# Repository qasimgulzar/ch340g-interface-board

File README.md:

# CH340G Interface Board

This repository contains the design files and documentation for a CH340G Interface Board, which is used to facilitate
communication between a computer and microcontroller-based projects via USB.

### Screenshots

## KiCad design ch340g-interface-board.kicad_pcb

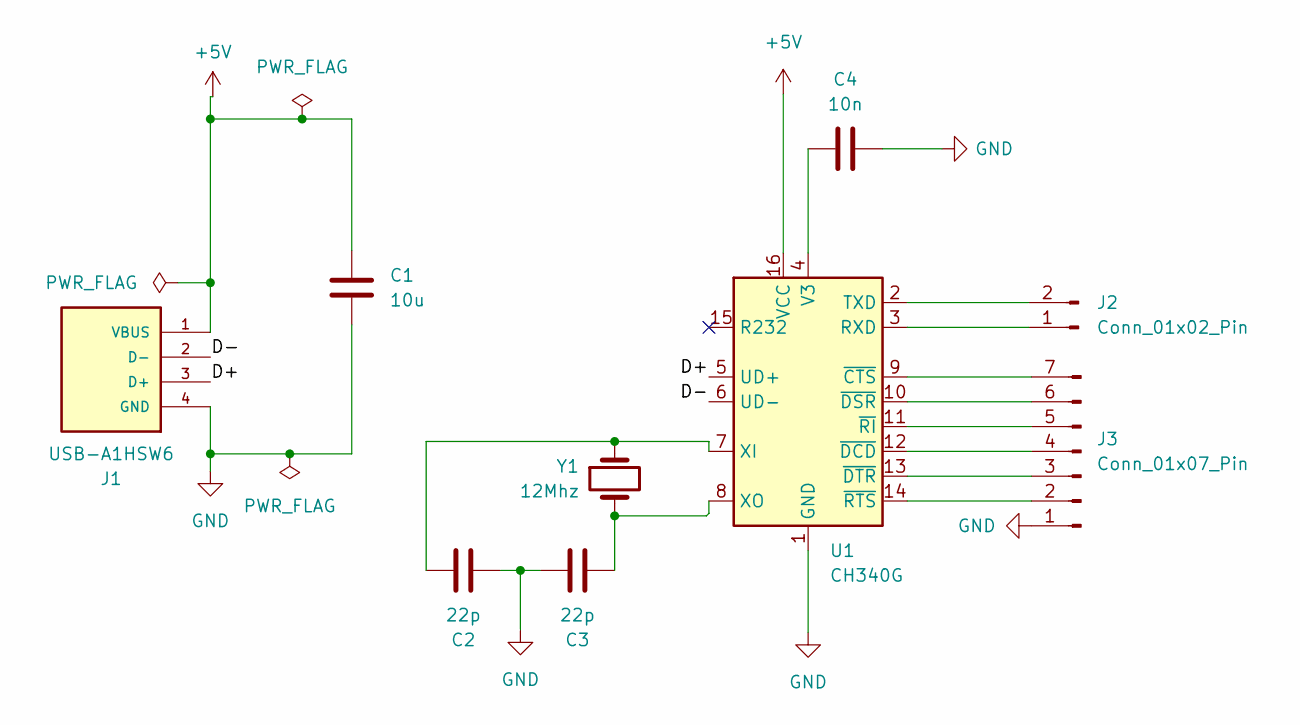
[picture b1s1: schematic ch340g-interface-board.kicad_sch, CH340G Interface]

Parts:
C1: 10u; CP_Radial_D4.0mm_P2.00mm
C2, C3: 22p; C_Disc_D3.0mm_W1.6mm_P2.50mm
C4: 10n; C_Disc_D3.0mm_W1.6mm_P2.50mm
J1: USB-A1HSW6; OST_USB-A1HSW6; PARTREV A
J2: Conn_01x02_Pin; PinHeader_1x02_P1.00mm_Vertical
J3: Conn_01x07_Pin; PinHeader_1x07_P1.00mm_Vertical
U1: CH340G; SOIC-16_3.9x9.9mm_P1.27mm
Y1: 12Mhz; Crystal_HC18-U_Vertical

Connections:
+5V: C1.1, J1.1 (VBUS), U1.16 (VCC)
/D+: J1.3 (D+), U1.5 (UD+)
/D-: J1.2 (D-), U1.6 (UD-)
GND: C1.2, C2.2, C3.1, C4.2, J1.4 (GND), J3.1, U1.1 (GND)
unnamed: J2.1, U1.3 (RXD)
unnamed: J2.2, U1.2 (TXD)
unnamed: J3.2, U1.14 (~RTS)
unnamed: J3.3, U1.13 (~DTR)
unnamed: J3.4, U1.12 (~DCD)
unnamed: J3.5, U1.11 (~RI)
unnamed: J3.6, U1.10 (~DSR)
unnamed: J3.7, U1.9 (~CTS)
unnamed: C4.1, U1.4 (V3)
unnamed: C2.1, U1.7 (XI), Y1.1
unnamed: C3.2, U1.8 (XO), Y1.2

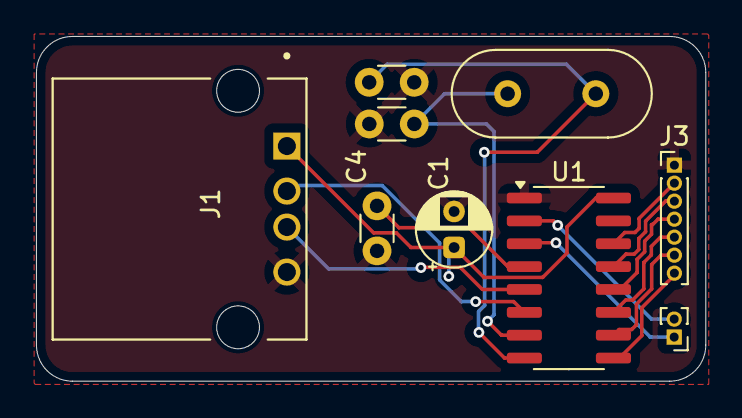
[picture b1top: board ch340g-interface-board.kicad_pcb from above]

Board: 2 copper layers, 37.2 x 19.2 mm, 9 parts (0 on the bottom side), 15 nets.

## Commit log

2025-09-30 feat: CH340G interface board
2025-09-30 documentation: update README.md
2025-10-01 documentation: board updates
